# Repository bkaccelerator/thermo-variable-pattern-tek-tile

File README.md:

# Thermo-variable Pattern TEK-TILE

A thermochromic dye makes fabric respond to heat by turning white.
Digitally-controlled heaters sewn into the material then allow the overall
pattern to be controlled by a computer.

One application is in augmented reality. The pattern can be tracked in space by
a device's camera to allow digital graphics to be overlaid. By varying the
pattern a garment can then communicate with devices using it for augmented
reality effects.

[TEK-TILES](https://bkaccelerator.com/research-all/t-lab/tek-tiles/) is a
project from the
[Brooklyn Fashion and Design Accelerator](https://bkaccelerator.com/) to develop
examples of new textile technologies.

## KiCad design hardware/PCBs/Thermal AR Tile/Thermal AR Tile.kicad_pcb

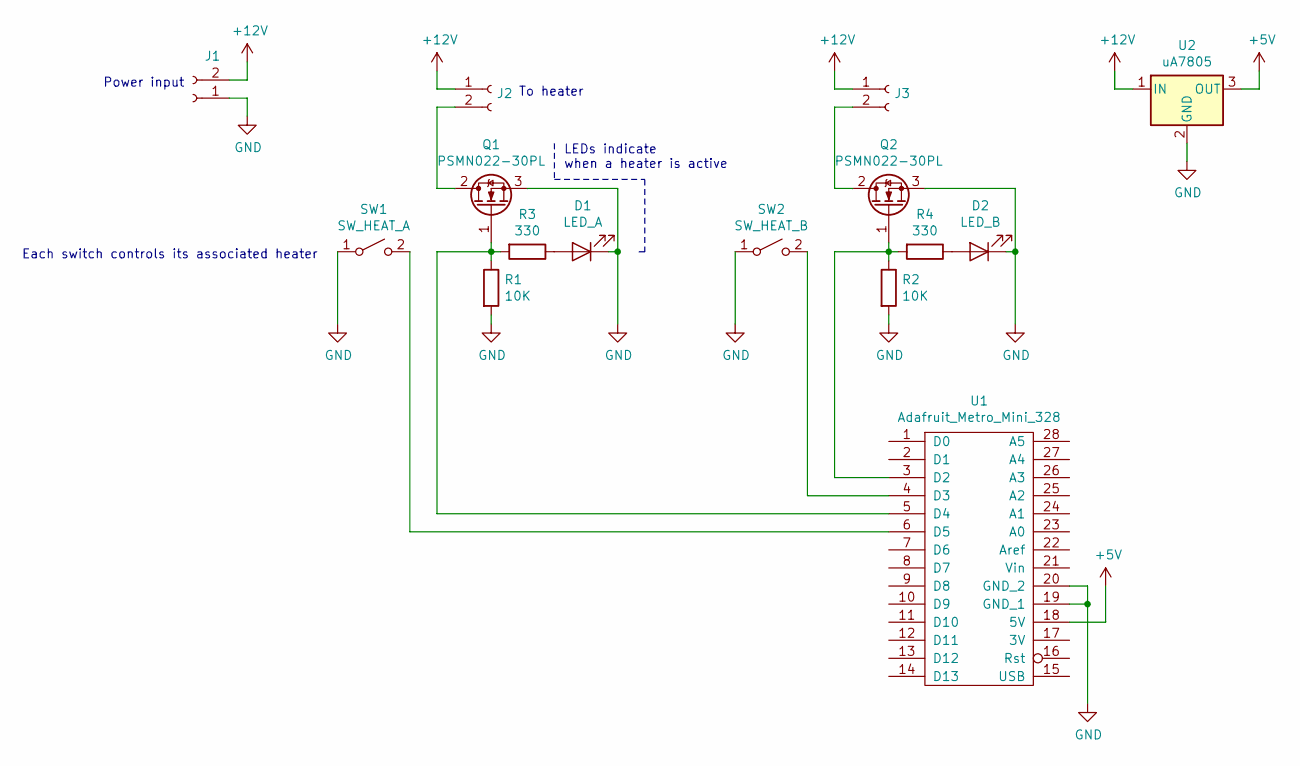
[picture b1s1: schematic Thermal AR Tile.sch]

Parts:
D1: LED_A; LED_D3.0mm
D2: LED_B; LED_D3.0mm
J1: Power_12V; PinHeader_1x02_P2.54mm_Vertical
J2: Heater2; PinHeader_1x02_P2.54mm_Vertical
J3: Heater1; PinHeader_1x02_P2.54mm_Vertical
Q1, Q2: PSMN022-30PL; TO-220-3_Horizontal_TabDown
R1, R2: 10K; R_Axial_DIN0207_L6.3mm_D2.5mm_P7.62mm_Horizontal
R3, R4: 330; R_Axial_DIN0207_L6.3mm_D2.5mm_P7.62mm_Horizontal
SW1: SW_HEAT_A; PinHeader_1x02_P2.54mm_Vertical
SW2: SW_HEAT_B; PinHeader_1x02_P2.54mm_Vertical
U1: Adafruit_Metro_Mini_328
U2: uA7805; TO-220-3_Horizontal_TabDown

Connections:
+5V: U1.18 (5V), U2.3 (OUT)
+12V: J1.2, J2.1, J3.1, U2.1 (IN)
GND: D1.1 (K), D2.1 (K), J1.1, Q1.3 (S), Q2.3 (S), R1.2, R2.2, SW1.1 (A), SW2.1 (A), U1.19 (GND_1), U1.20 (GND_2), U2.2 (GND)
unnamed: D1.2 (A), R3.1
unnamed: D2.2 (A), R4.1
unnamed: J2.2, Q1.2 (D)
unnamed: J3.2, Q2.2 (D)
unnamed: Q1.1 (G), R1.1, R3.2, U1.5 (D4)
unnamed: Q2.1 (G), R2.1, R4.2, U1.3 (D2)
unnamed: SW1.2 (B), U1.6 (D5)
unnamed: SW2.2 (B), U1.4 (D3)

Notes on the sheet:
Each switch controls its associated heater
LEDs indicate when a heater is active
To heater
Power input

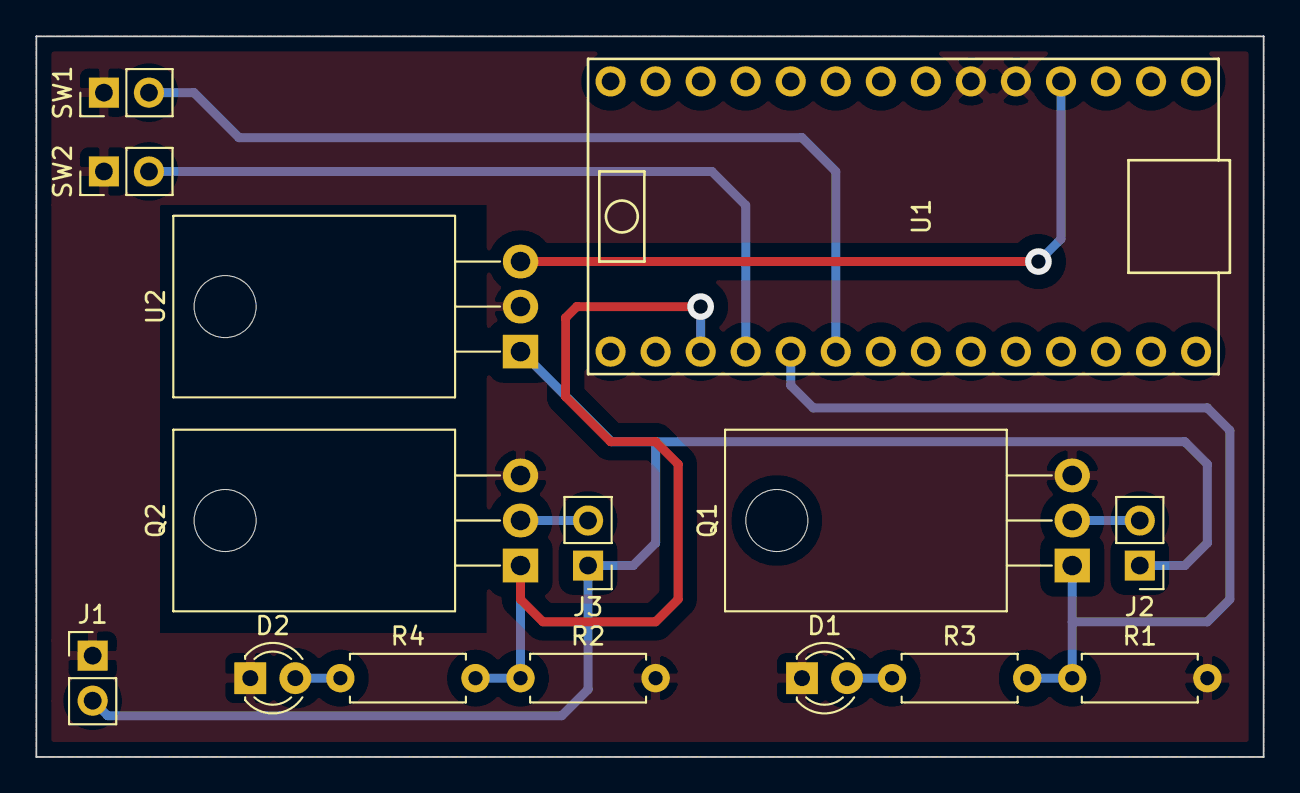
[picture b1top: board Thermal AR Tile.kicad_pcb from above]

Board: 2 copper layers, 69.2 x 40.6 mm, 15 parts (0 on the bottom side), 11 nets.

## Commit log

2019-06-10 Snapshot
